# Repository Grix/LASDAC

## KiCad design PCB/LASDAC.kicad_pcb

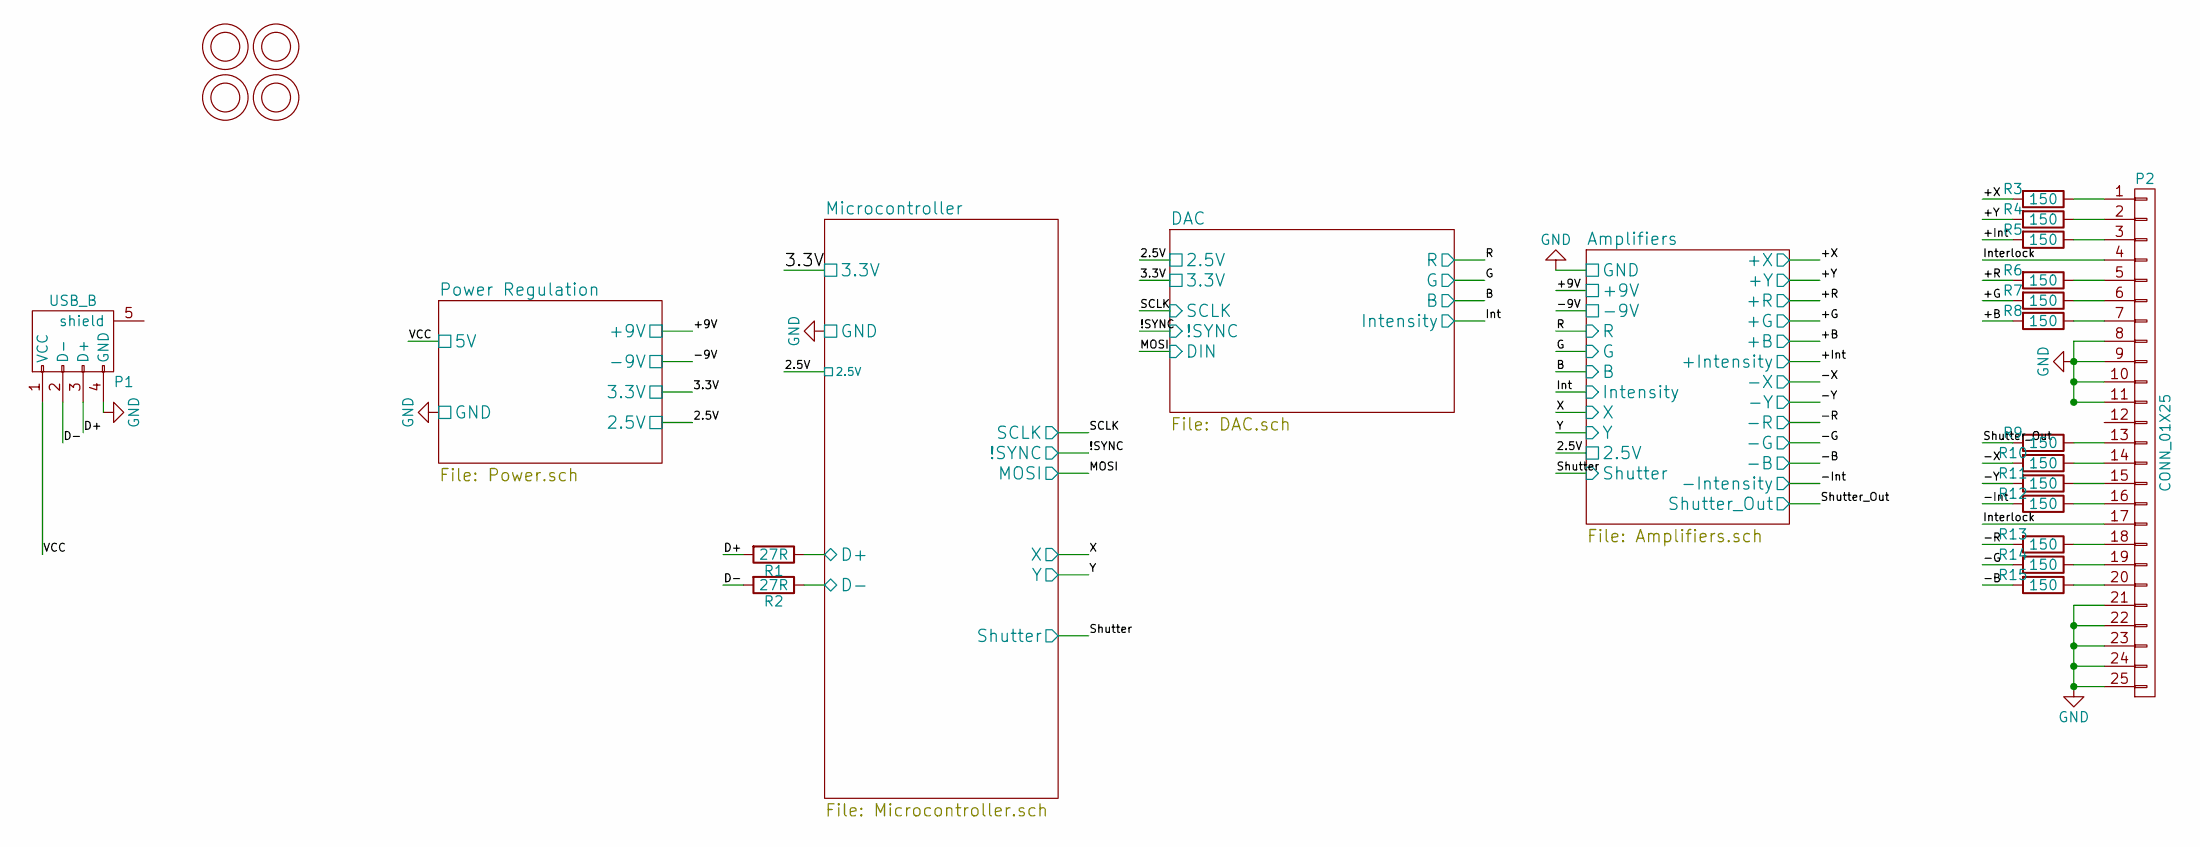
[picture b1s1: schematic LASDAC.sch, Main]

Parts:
H1, H2, H3, H4: Mounting_Hole; MountingHole_3.2mm_M3
P1: USB_B
P2: CONN_01X25; DB25FC
R1, R2: 27R; R_0805
R3, R4, R5, R6, R7, R8, R9, R10, R11, R12, R13, R14, R15: 150; R_0805

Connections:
/Amplifiers/+B: R8.2; also elsewhere on the board
/Amplifiers/+G: R7.2; also elsewhere on the board
/Amplifiers/+Intensity: R5.2; also elsewhere on the board
/Amplifiers/+R: R6.2; also elsewhere on the board
/Amplifiers/+X: R3.2; also elsewhere on the board
/Amplifiers/+Y: R4.2; also elsewhere on the board
/Amplifiers/-B: R15.2; also elsewhere on the board
/Amplifiers/-G: R14.2; also elsewhere on the board
/Amplifiers/-Intensity: R12.2; also elsewhere on the board
/Amplifiers/-R: R13.2; also elsewhere on the board
/Amplifiers/-X: R10.2; also elsewhere on the board
/Amplifiers/-Y: R11.2; also elsewhere on the board
/Amplifiers/Shutter_Out: R9.2; also elsewhere on the board
/D+: P1.3 (D+), R1.2
/D-: P1.2 (D-), R2.2
/Interlock: P2.4, P2.17
/Microcontroller/D+: R1.1; also elsewhere on the board
/Microcontroller/D-: R2.1; also elsewhere on the board
/Power Regulation/5V: P1.1 (VCC); also elsewhere on the board
GND: P1.4 (GND), P2.8, P2.9, P2.10, P2.11, P2.21, P2.22, P2.23, P2.24, P2.25; also elsewhere on the board
unnamed: P2.1, R3.1
unnamed: P2.2, R4.1
unnamed: P2.3, R5.1
unnamed: P2.5, R6.1
unnamed: P2.6, R7.1
unnamed: P2.7, R8.1
unnamed: P2.13, R9.1
unnamed: P2.14, R10.1
unnamed: P2.15, R11.1
unnamed: P2.16, R12.1
unnamed: P2.18, R13.1
unnamed: P2.19, R14.1
unnamed: P2.20, R15.1

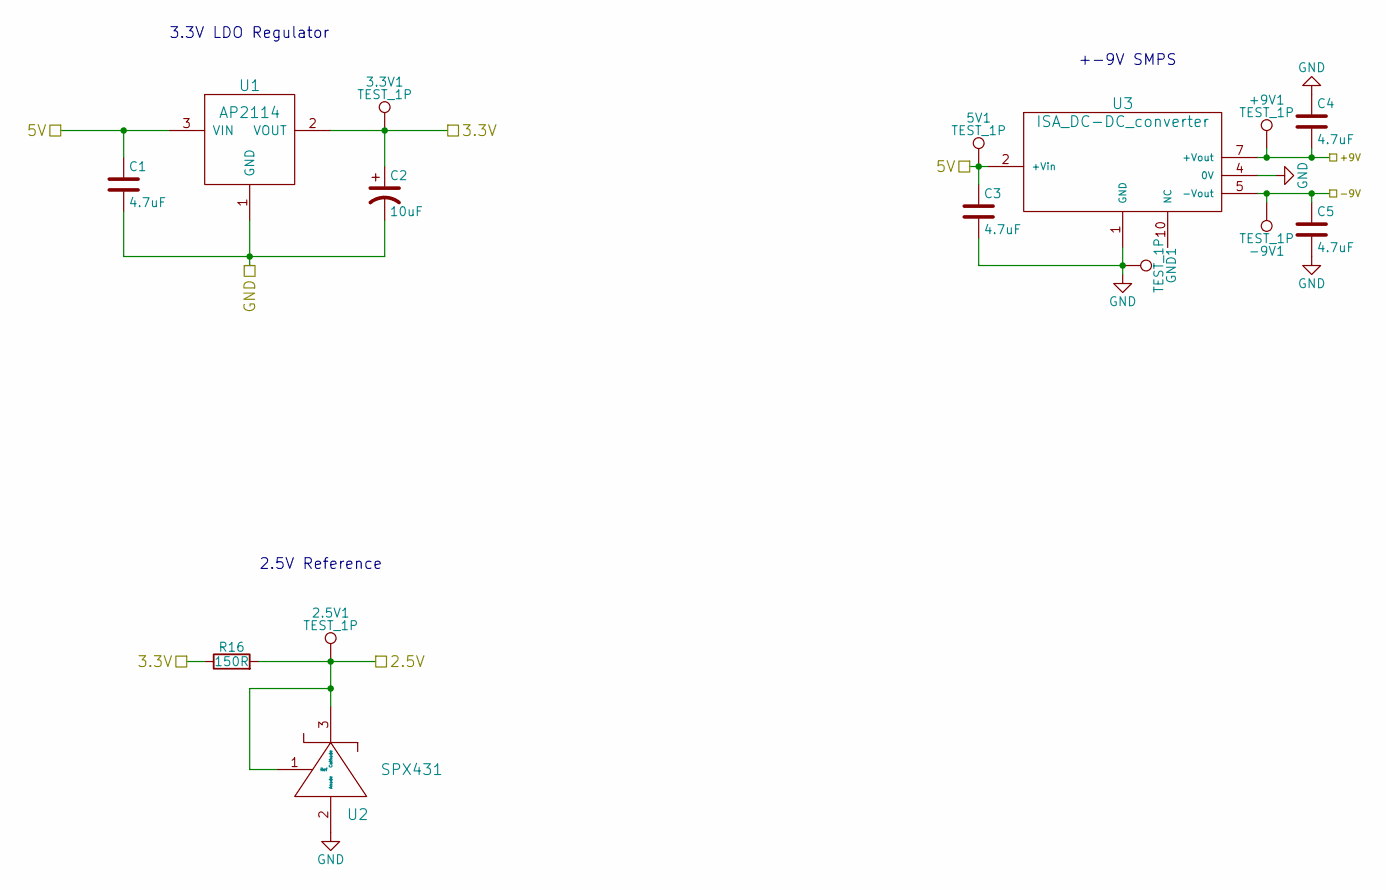
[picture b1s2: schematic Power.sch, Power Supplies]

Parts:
2.5V1, 3.3V1, 5V1: TEST_1P; Measurement_Point_Round-SMD-Pad_Big
+9V1: TEST_1P; Measurement_Point_Round-SMD-Pad_Big
-9V1: TEST_1P; Measurement_Point_Round-SMD-Pad_Big
C1, C4, C5: 4.7uF; C_0603
C2: 10uF
C3: 4.7uF; c_elec_4x5.8
GND1: TEST_1P; Measurement_Point_Round-SMD-Pad_Big
R16: 150R; R_0805
U1: AP2114; SOT-223
U2: SPX431; SOT89-3_Housing
U3: ISA_DC-DC_converter; SOIC-10

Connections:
/Amplifiers/2.5V: 2.5V1.1, R16.2, U2.1 (Ref), U2.3 (Cathode); also elsewhere on the board
/Amplifiers/+9V: +9V1.1, C4.2, U3.7 (+Vout); also elsewhere on the board
/Amplifiers/-9V: -9V1.1, C5.1, U3.5 (-Vout); also elsewhere on the board
/DAC/3.3V: 3.3V1.1, C2.1, R16.1, U1.2 (VOUT); also elsewhere on the board
/Power Regulation/5V: 5V1.1, C1.1, C3.1, U1.3 (VIN), U3.2 (+Vin); also elsewhere on the board
GND: C1.2, C2.2, C3.2, C4.1, C5.2, GND1.1, U1.1 (GND), U2.2 (Anode), U3.1 (GND), U3.4 (0V); also elsewhere on the board

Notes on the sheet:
3.3V LDO Regulator
+-9V SMPS
2.5V Reference

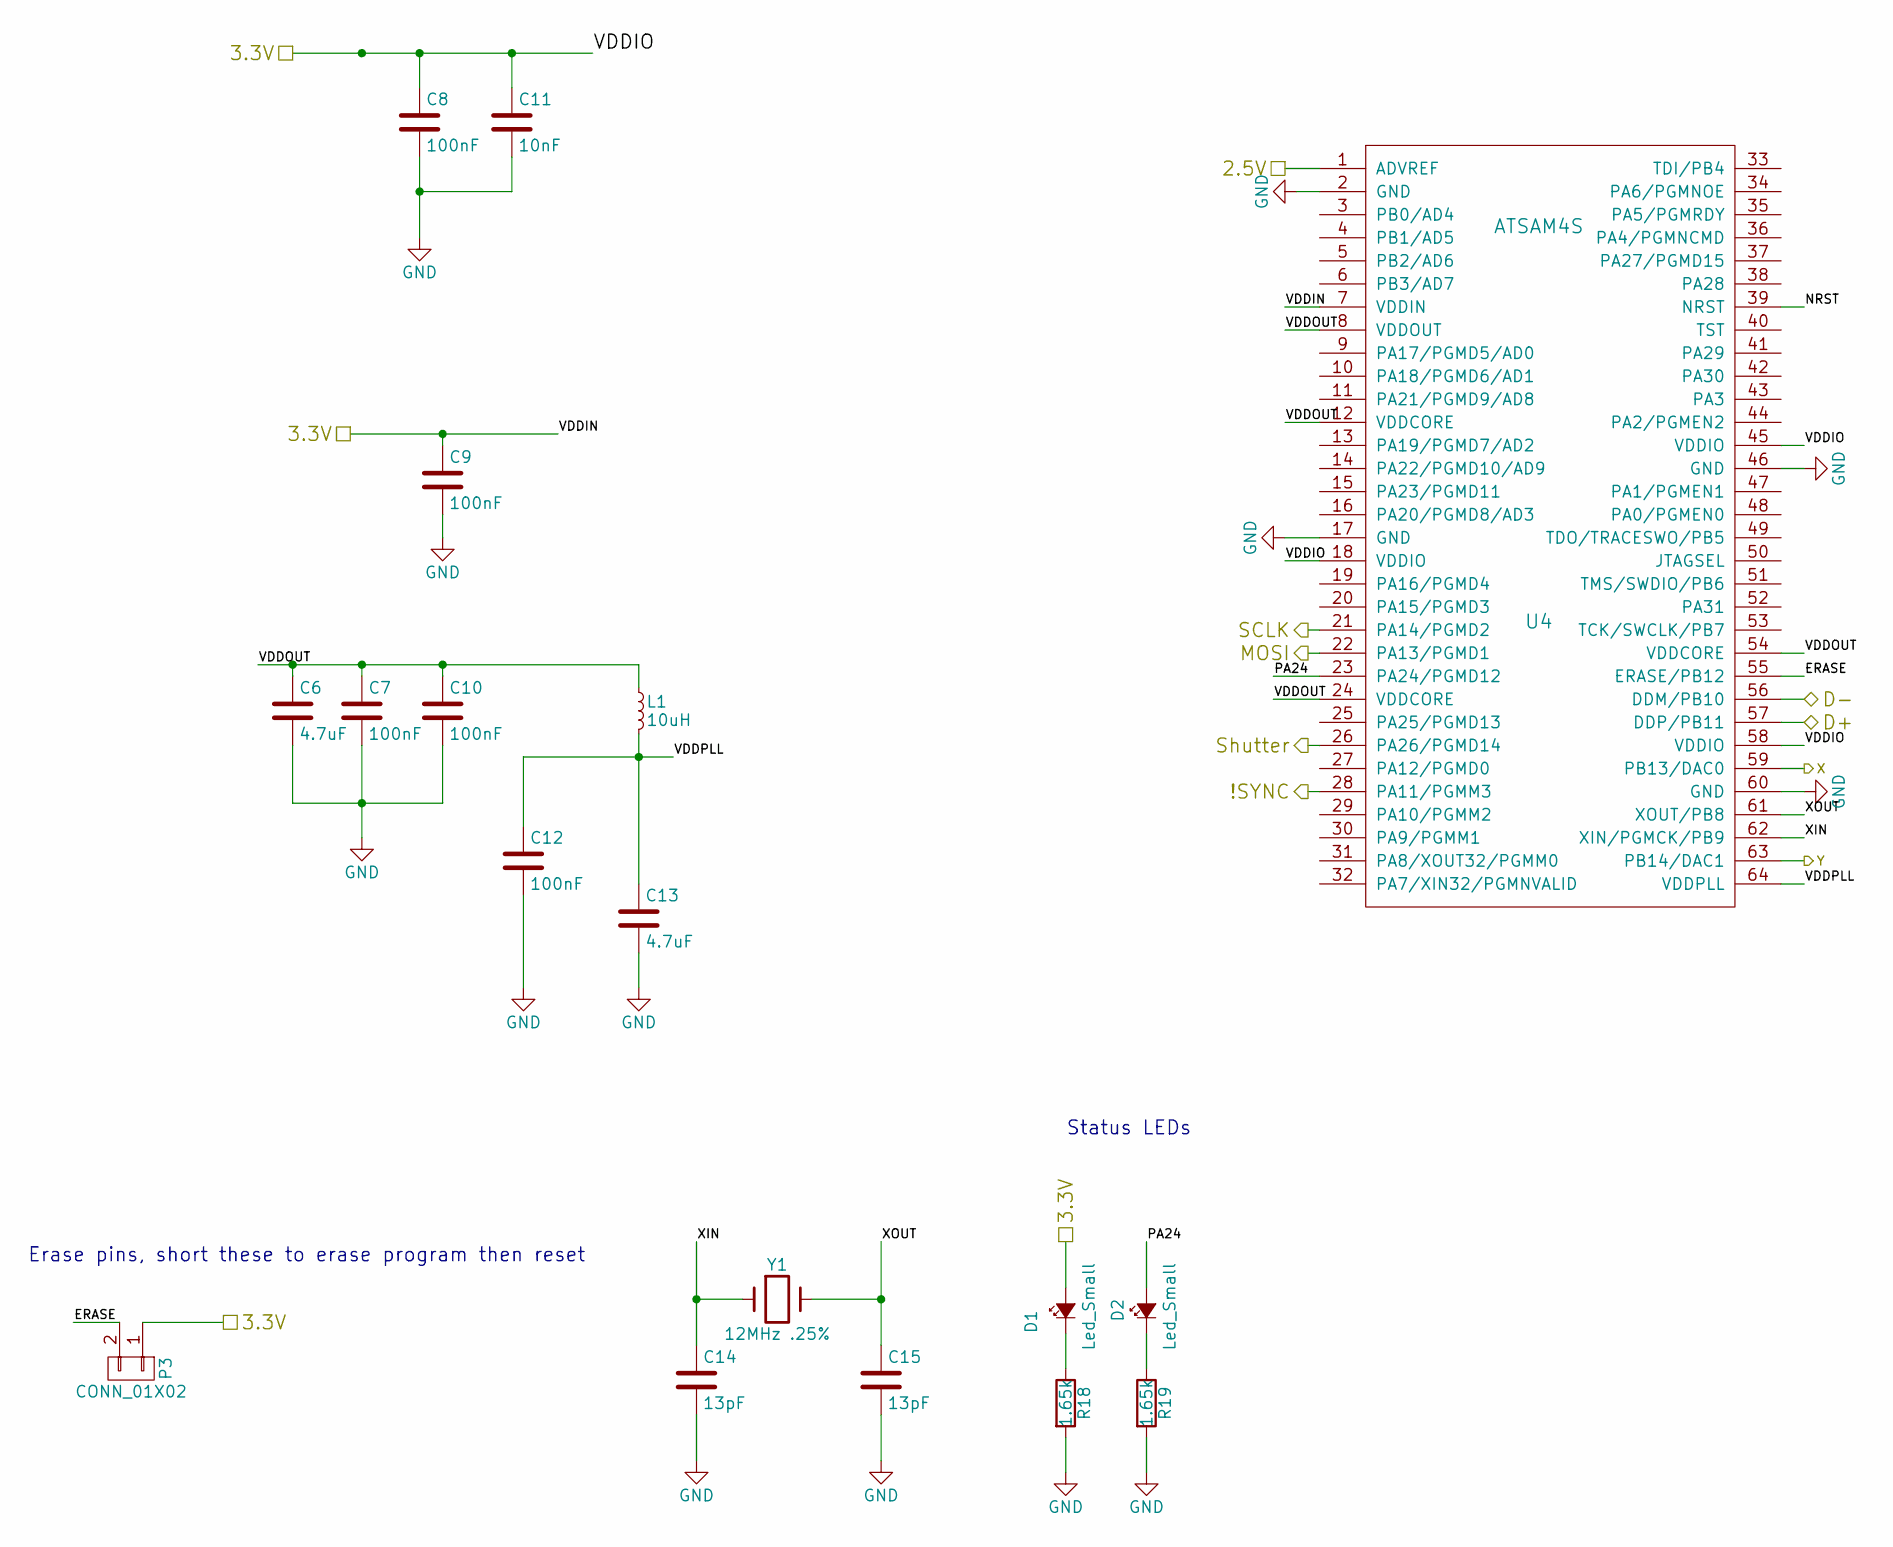
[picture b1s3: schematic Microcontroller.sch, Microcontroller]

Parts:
C6, C13: 4.7uF; C_0603
C7, C8, C9, C10, C12: 100nF; C_0402
C11: 10nF; C_0402
C14, C15: 13pF; C_0402
D1, D2: Led_Small; LED_0603
L1: 10uH; Inductor_SM_1008i2520m
P3: CONN_01X02
R18, R19: 1.65k; R_0805
U4: ATSAM4S; LQFP-64_10x10mm_Pitch0.5mm
Y1: 12MHz .25%; Crystal_HC49-SD_SMD

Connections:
/Amplifiers/2.5V: U4.1 (ADVREF); also elsewhere on the board
/Amplifiers/Shutter: U4.26 (PA26/PGMD14); also elsewhere on the board
/Amplifiers/X: U4.59 (PB13/DAC0); also elsewhere on the board
/Amplifiers/Y: U4.63 (PB14/DAC1); also elsewhere on the board
/DAC/3.3V: C8.1, C9.1, C11.1, D1.2 (A), P3.1, U4.7 (VDDIN), U4.18 (VDDIO), U4.45 (VDDIO), U4.58 (VDDIO); also elsewhere on the board
/DAC/!SYNC: U4.28 (PA11/PGMM3); also elsewhere on the board
/DAC/Din: U4.22 (PA13/PGMD1); also elsewhere on the board
/DAC/SCLK: U4.21 (PA14/PGMD2); also elsewhere on the board
/Microcontroller/D+: U4.57 (DDP/PB11); also elsewhere on the board
/Microcontroller/D-: U4.56 (DDM/PB10); also elsewhere on the board
/Microcontroller/ERASE: P3.2, U4.55 (ERASE/PB12); also elsewhere on the board
/Microcontroller/NRST: U4.39 (NRST)
/Microcontroller/PA24: D2.2 (A), U4.23 (PA24/PGMD12)
/Microcontroller/VDDOUT: C6.1, C7.1, C10.1, L1.1, U4.8 (VDDOUT), U4.12 (VDDCORE), U4.24 (VDDCORE), U4.54 (VDDCORE)
/Microcontroller/VDDPLL: C12.1, C13.1, L1.2, U4.64 (VDDPLL)
/Microcontroller/XIN: C14.1, U4.62 (XIN/PGMCK/PB9), Y1.1
/Microcontroller/XOUT: C15.1, U4.61 (XOUT/PB8), Y1.2
GND: C6.2, C7.2, C8.2, C9.2, C10.2, C11.2, C12.2, C13.2, C14.2, C15.2, R18.2, R19.2, U4.2 (GND), U4.17 (GND), U4.46 (GND), U4.60 (GND); also elsewhere on the board
unnamed: D1.1 (K), R18.1
unnamed: D2.1 (K), R19.1

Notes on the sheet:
Erase pins, short these to erase program then reset
Status LEDs

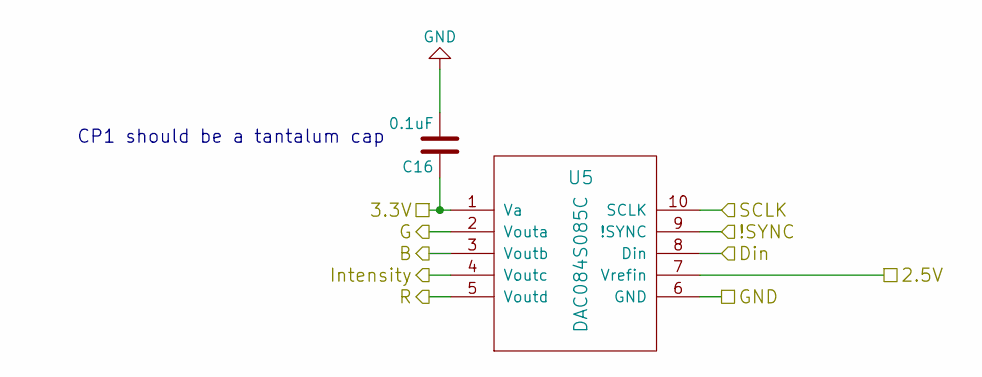
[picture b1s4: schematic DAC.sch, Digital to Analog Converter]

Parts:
C16: 0.1uF; C_0402
U5: DAC084S085C; MSOP-10_3x3mm_Pitch0.5mm

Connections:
/Amplifiers/2.5V: U5.7 (Vrefin); also elsewhere on the board
/Amplifiers/+B: U5.3 (Voutb); also elsewhere on the board
/Amplifiers/+G: U5.2 (Vouta); also elsewhere on the board
/Amplifiers/+Intensity: U5.4 (Voutc); also elsewhere on the board
/Amplifiers/+R: U5.5 (Voutd); also elsewhere on the board
/DAC/3.3V: C16.1, U5.1 (Va); also elsewhere on the board
/DAC/!SYNC: U5.9 (!SYNC); also elsewhere on the board
/DAC/Din: U5.8 (Din); also elsewhere on the board
/DAC/SCLK: U5.10 (SCLK); also elsewhere on the board
GND: C16.2, U5.6 (GND); also elsewhere on the board

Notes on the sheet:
CP1 should be a tantalum cap

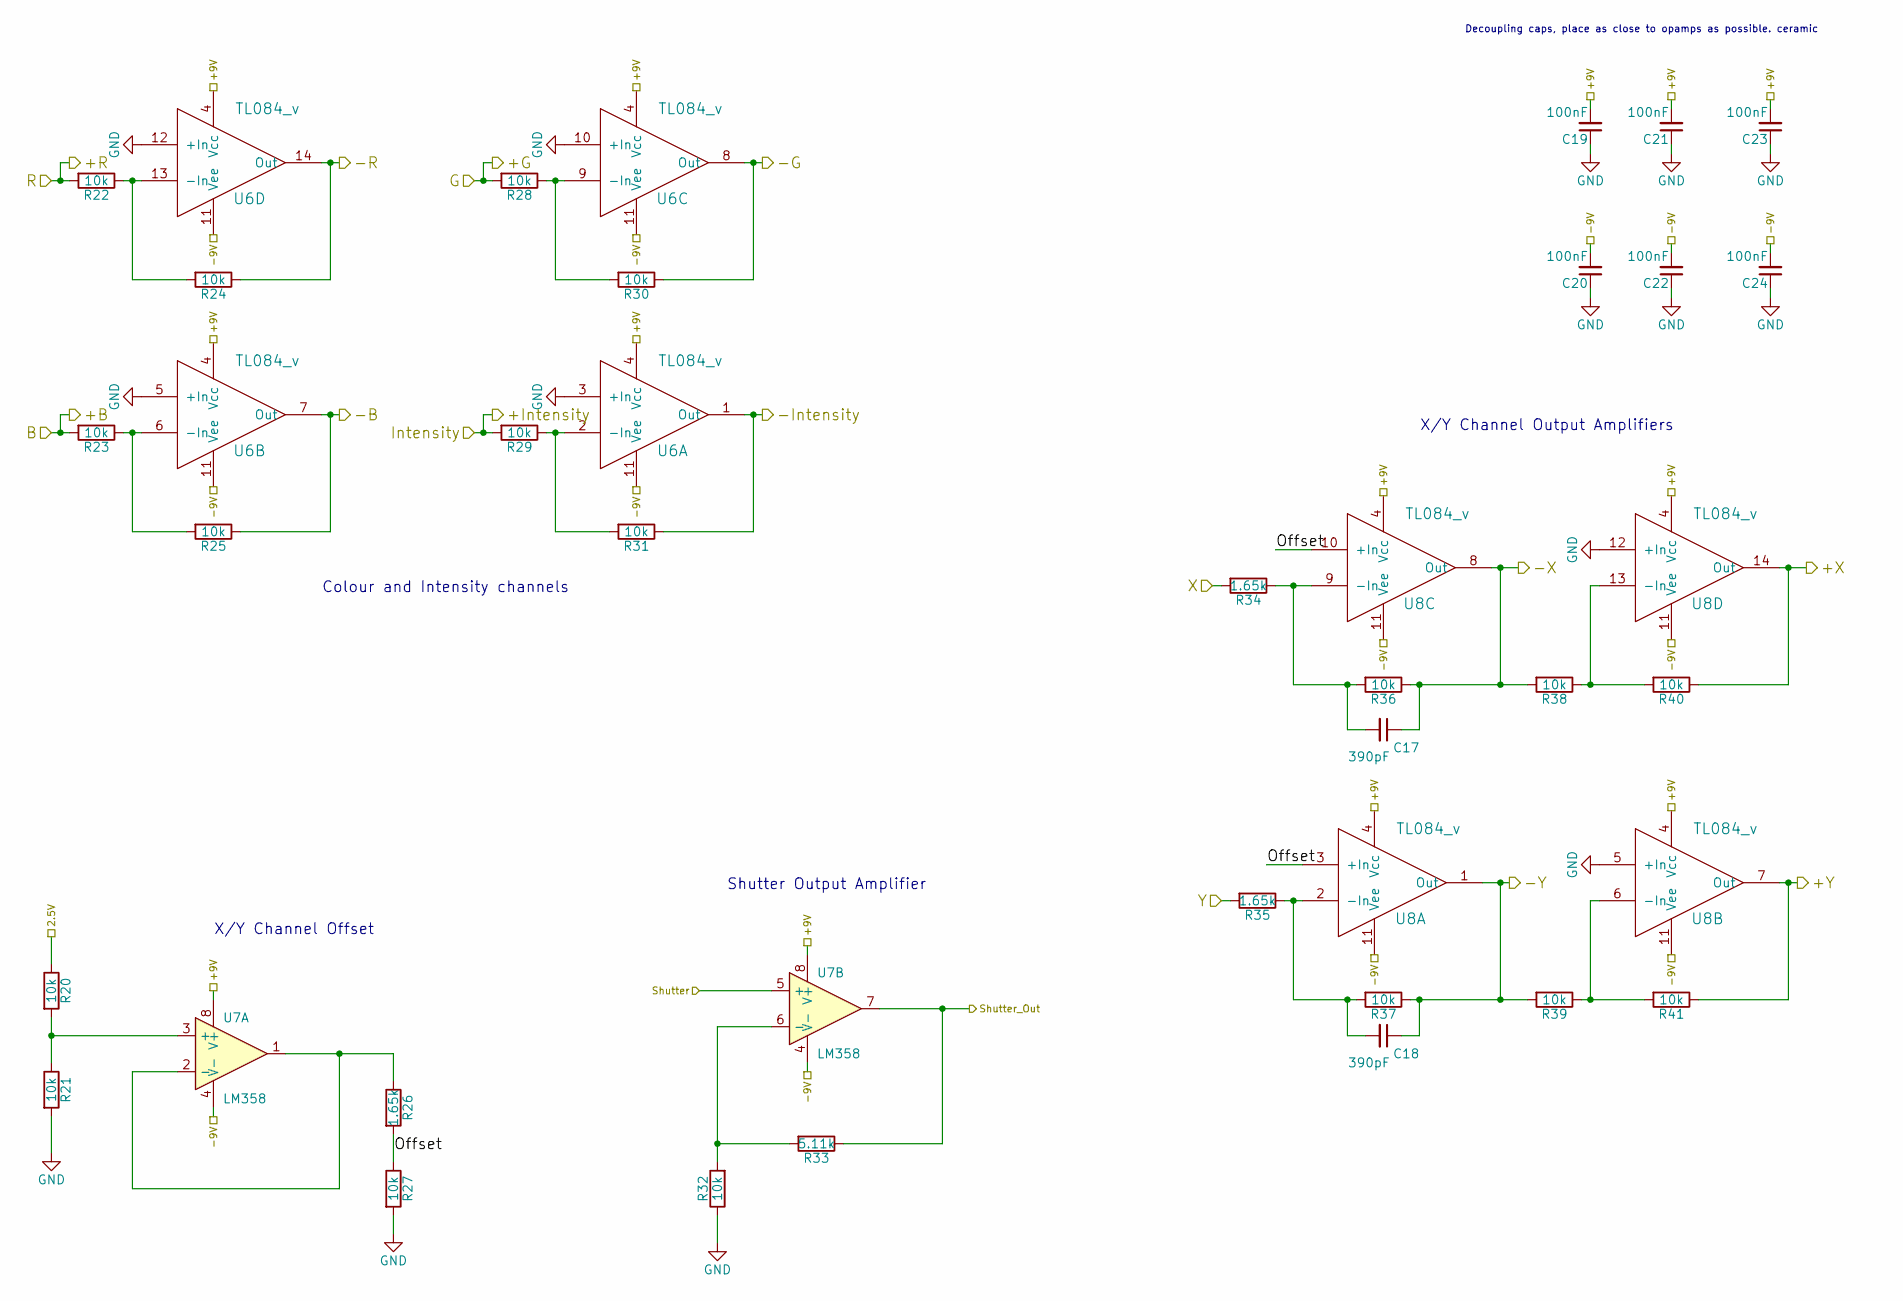
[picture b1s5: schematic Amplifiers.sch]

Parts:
C17, C18: 390pF; C_0402
C19, C20, C21, C22, C23, C24: 100nF; C_0402
R20, R21, R22, R23, R24, R25, R27, R28, R29, R30, R31, R32, R36, R37, R38, R39, R40, R41: 10k; R_0805
R26, R34, R35: 1.65k; R_0805
R33: 5.11k; R_0805
U6, U8: TL084_v; TSSOP-14_4.4x5mm_Pitch0.65mm
U7: LM358; SOIC-8_3.9x4.9mm_Pitch1.27mm

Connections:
/Amplifiers/2.5V: R20.1; also elsewhere on the board
/Amplifiers/+9V: C19.2, C21.2, C23.2, U6.4 (Vcc), U7.8 (V+), U8.4 (Vcc); also elsewhere on the board
/Amplifiers/+B: R23.2; also elsewhere on the board
/Amplifiers/+G: R28.2; also elsewhere on the board
/Amplifiers/+Intensity: R29.2; also elsewhere on the board
/Amplifiers/+R: R22.2; also elsewhere on the board
/Amplifiers/+X: R40.1, U8.14 (Out); also elsewhere on the board
/Amplifiers/+Y: R41.1, U8.7 (Out); also elsewhere on the board
/Amplifiers/-9V: C20.2, C22.2, C24.2, U6.11 (Vee), U7.4 (V-), U8.11 (Vee); also elsewhere on the board
/Amplifiers/-B: R25.1, U6.7 (Out); also elsewhere on the board
/Amplifiers/-G: R30.1, U6.8 (Out); also elsewhere on the board
/Amplifiers/-Intensity: R31.1, U6.1 (Out); also elsewhere on the board
/Amplifiers/-R: R24.1, U6.14 (Out); also elsewhere on the board
/Amplifiers/-X: C17.1, R36.1, R38.2, U8.8 (Out); also elsewhere on the board
/Amplifiers/-Y: C18.1, R37.1, R39.2, U8.1 (Out); also elsewhere on the board
/Amplifiers/Offset: R26.2, R27.1, U8.3 (+In), U8.10 (+In)
/Amplifiers/Shutter: U7.5 (+); also elsewhere on the board
/Amplifiers/Shutter_Out: R33.1, U7.7; also elsewhere on the board
/Amplifiers/X: R34.2; also elsewhere on the board
/Amplifiers/Y: R35.2; also elsewhere on the board
GND: C19.1, C20.1, C21.1, C22.1, C23.1, C24.1, R21.2, R27.2, R32.1, U6.3 (+In), U6.5 (+In), U6.10 (+In), U6.12 (+In), U8.5 (+In), U8.12 (+In); also elsewhere on the board
unnamed: C17.2, R34.1, R36.2, U8.9 (-In)
unnamed: C18.2, R35.1, R37.2, U8.2 (-In)
unnamed: R20.2, R21.1, U7.3 (+)
unnamed: R22.1, R24.2, U6.13 (-In)
unnamed: R23.1, R25.2, U6.6 (-In)
unnamed: R26.1, U7.1, U7.2 (-)
unnamed: R28.1, R30.2, U6.9 (-In)
unnamed: R29.1, R31.2, U6.2 (-In)
unnamed: R32.2, R33.2, U7.6 (-)
unnamed: R38.1, R40.2, U8.13 (-In)
unnamed: R39.1, R41.2, U8.6 (-In)

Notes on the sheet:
Decoupling caps, place as close to opamps as possible. ceramic
Colour and Intensity channels
Shutter Output Amplifier
X/Y Channel Offset
X/Y Channel Output Amplifiers

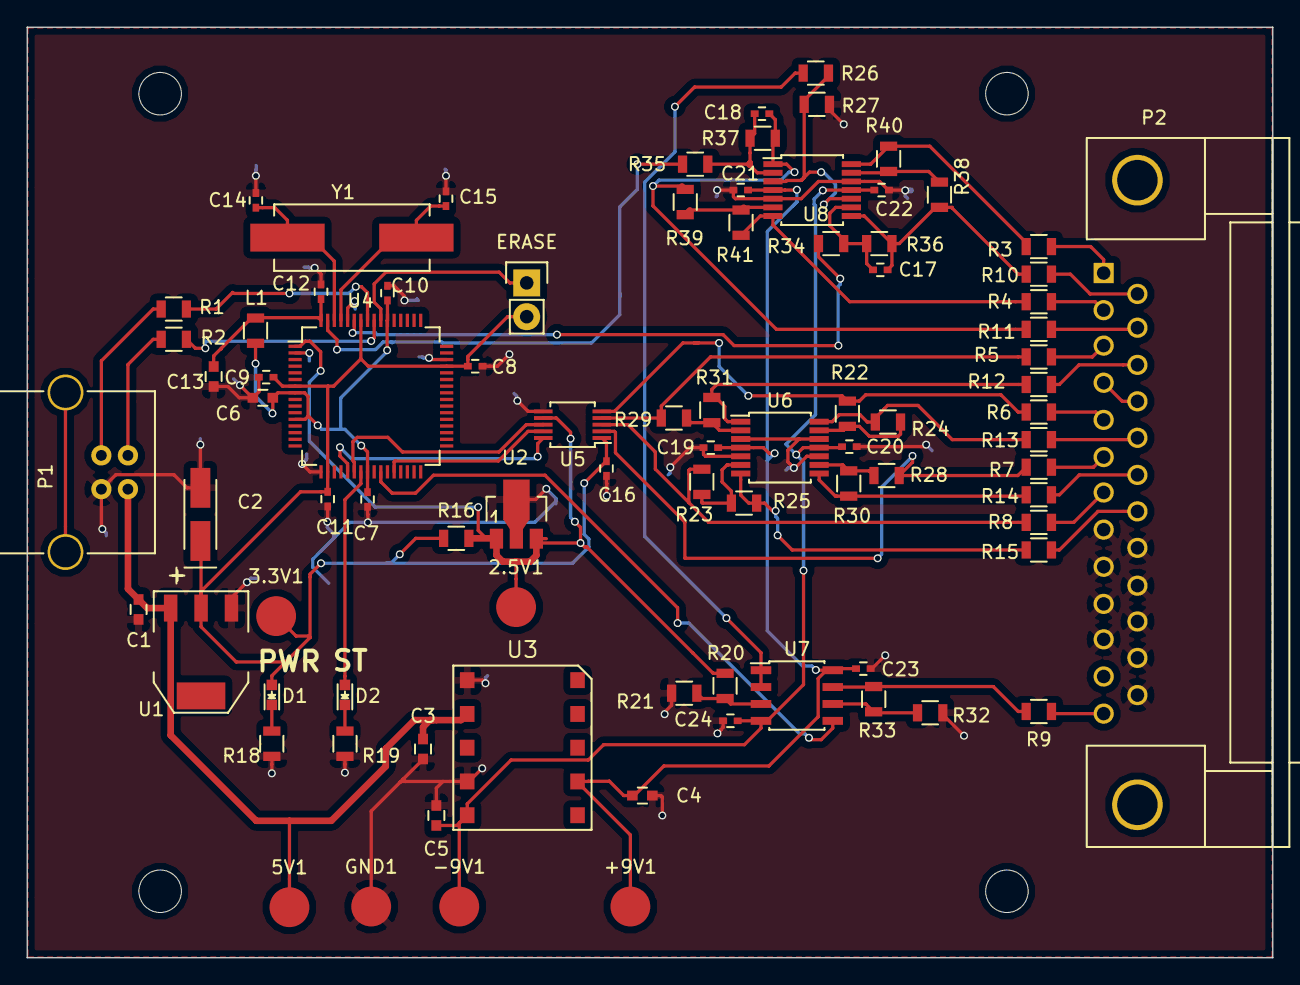
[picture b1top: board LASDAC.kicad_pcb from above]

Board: 2 copper layers, 93.7 x 70.0 mm, 89 parts (0 on the bottom side), 63 nets.

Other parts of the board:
ERASE: SW_PUSH; Pin_Header_Straight_1x02

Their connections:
/DAC/3.3V: ERASE.2; also elsewhere on the board
/Microcontroller/ERASE: ERASE.1; also elsewhere on the board

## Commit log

2016-01-24 arduino branch template AS project
2016-01-25 added point type and started point output function
2016-01-26 output_point() reads from array pointer
2016-02-04 addeds SPI, blank&center function, started state machine
2016-02-05 test output state
2016-02-05 finished frame output
2016-02-06 added shutter and led io functions
2016-02-08 start and stop functions and states
2016-02-10 hardcoded test frame
2016-02-16 no more state machine
2016-02-16 Set frame size for testing
2016-02-16 started usb isoch. transfer ISR process
2016-02-19 change some stuff to fit flowchart v2 and ready for lab testing
2016-02-20 fixed testframe, renamed playing flag
2016-02-24 test frame stuff
2016-02-26 continued implementation of usb iso ISR
2016-02-28 finished usb iso ISR placeholder, not tested
2016-02-29 polished usb iso ISR, started usb control ISR, more documentation
2016-03-01 some error handling and bug fixes
2016-03-03 new gradient testframe
2016-03-03 added not-finished ltspice correction amp circuit
2016-03-03 tl084 ltspice lib
2016-03-06 remove math.h dep. and usb control protocol fix
2016-03-06 simuleringsfiler med direkte DAC output og ledningssimulering
2016-03-08 adjusted correction amp circuits
2016-03-08 added SMPS schematic and models
2016-03-09 combined circuits
2016-03-09 byttet om på + og - forsyning
2016-03-10 små endringer, fungere ikke
2016-03-10 smps fungerer men ustabil ved høyt strømtrekk
2016-03-11 endringer for smps
2016-03-13 small smps changes
2016-03-16 fixed testframe
2016-03-18 startet usb mappen
2016-03-21 added usb module to AS project
2016-03-25 basic usb frame handling, not tested
2016-03-29 removed smps circuit
2016-04-01 sam4s2b firmware project porting started
2016-04-08 added PCB schematic and board files
    Kicad project with part libraries included.
    TODO: Backwards annotation from PCB to schematic
2016-04-12 sam4s project
2016-04-12 Generated BOM, fixed component names in schematic
    Changed component names on output resistors and status LED to match that
    in PCB
2016-04-12 Reannotated Components
    Annotated components to standards,
    TODO: Add Silkscreen for signals on bottom
2016-04-13 fixing sam4s board config
2016-04-15 fixed usb callback function
2016-04-15 Replaced L1 footprint, changed Resistor values
2016-04-17 Fixed schematic errors, "small" changes to PCB
    Flipped DAC, changed component values, removed 1 capacitor, moved c16
    from vref to power. Developed an urge to kill kicad
2016-04-17 Plotted Gerbers
2016-04-17 generated drill file
2016-04-17 Resized board
    Resized board to be shorter than 100mm
2016-04-17 Added solder paste layers
2016-04-17 endrer gerber navn
2016-04-20 kopierte usb med konfig til gitle-pc, og endret klokkeconfig i sam4s prosjekt
2016-04-20 usb testprosjekt for gitle
2016-04-21 fungerende usb bulk test
2016-04-22 usb og endringer i arduino firmware
2016-04-26 firmware endret til ny bildestruktur (8-byte)
2016-04-29 finished control (interrupt) transfer handling in arduino firmware, tweaks
2016-05-03 Started driver folder
2016-05-03 changed to win32
2016-05-04 usb driver testing
2016-05-04 remove bloat
2016-05-06 skifte til pure uint8_t istedet for struct
2016-05-06 changed some code
2016-05-06 fixed errors
2016-05-06 fixed more errors
2016-05-07 8 bug i firmware
2016-05-07 firmware polishing
2016-05-11 fixed even more errors
2016-05-11 lastet opp presentasjon til 12.
2016-05-11 sam4s2b implementation of updated firmware
2016-05-11 change clock settings + reorganize
2016-05-21 usb test
2016-05-21 working firmware?
2016-05-22 disable watchdog
2016-05-22 sleepmgr fixes (but still going to sleep?)
2016-05-24 polish
2016-05-25 fix sync bug
2016-05-27 cleanup and memory optimizations
2016-05-28 firmware memory optimizations
